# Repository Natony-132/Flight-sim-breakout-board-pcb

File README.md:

# Flight simulator control integration PCB 

This project was to make a simple, expandable, Hardware to USB input control board. This is so that additional, non-standard controls or switch panels can be added to an existing flight simulator setup. 

This was accomplished by using an existing Arduino program called FreeJoy with a custom Interface board. The freeJoy program allows a series of Shift registers to expand the number of inputs that an arduino can normally except. 

This custom PCB was designed with 40 inputs for switches and pads for up to 4 potentiometers.  

Due to signal noise in most potentiometers, each pad was designed to have a 3rd order filter built in. 

This proved to be unnecessary due to filters built into the Arduino program. This was not unexpected, so a filter bypass was built into the PCB so that the physical filter doesn't need to not be populated during board assembly. 

Later iterations will leave off this filter entirely.

These custom circuit boards were used in a UH-34 Sikorsky helicopter collective and a replica FA18 landing gear panel.

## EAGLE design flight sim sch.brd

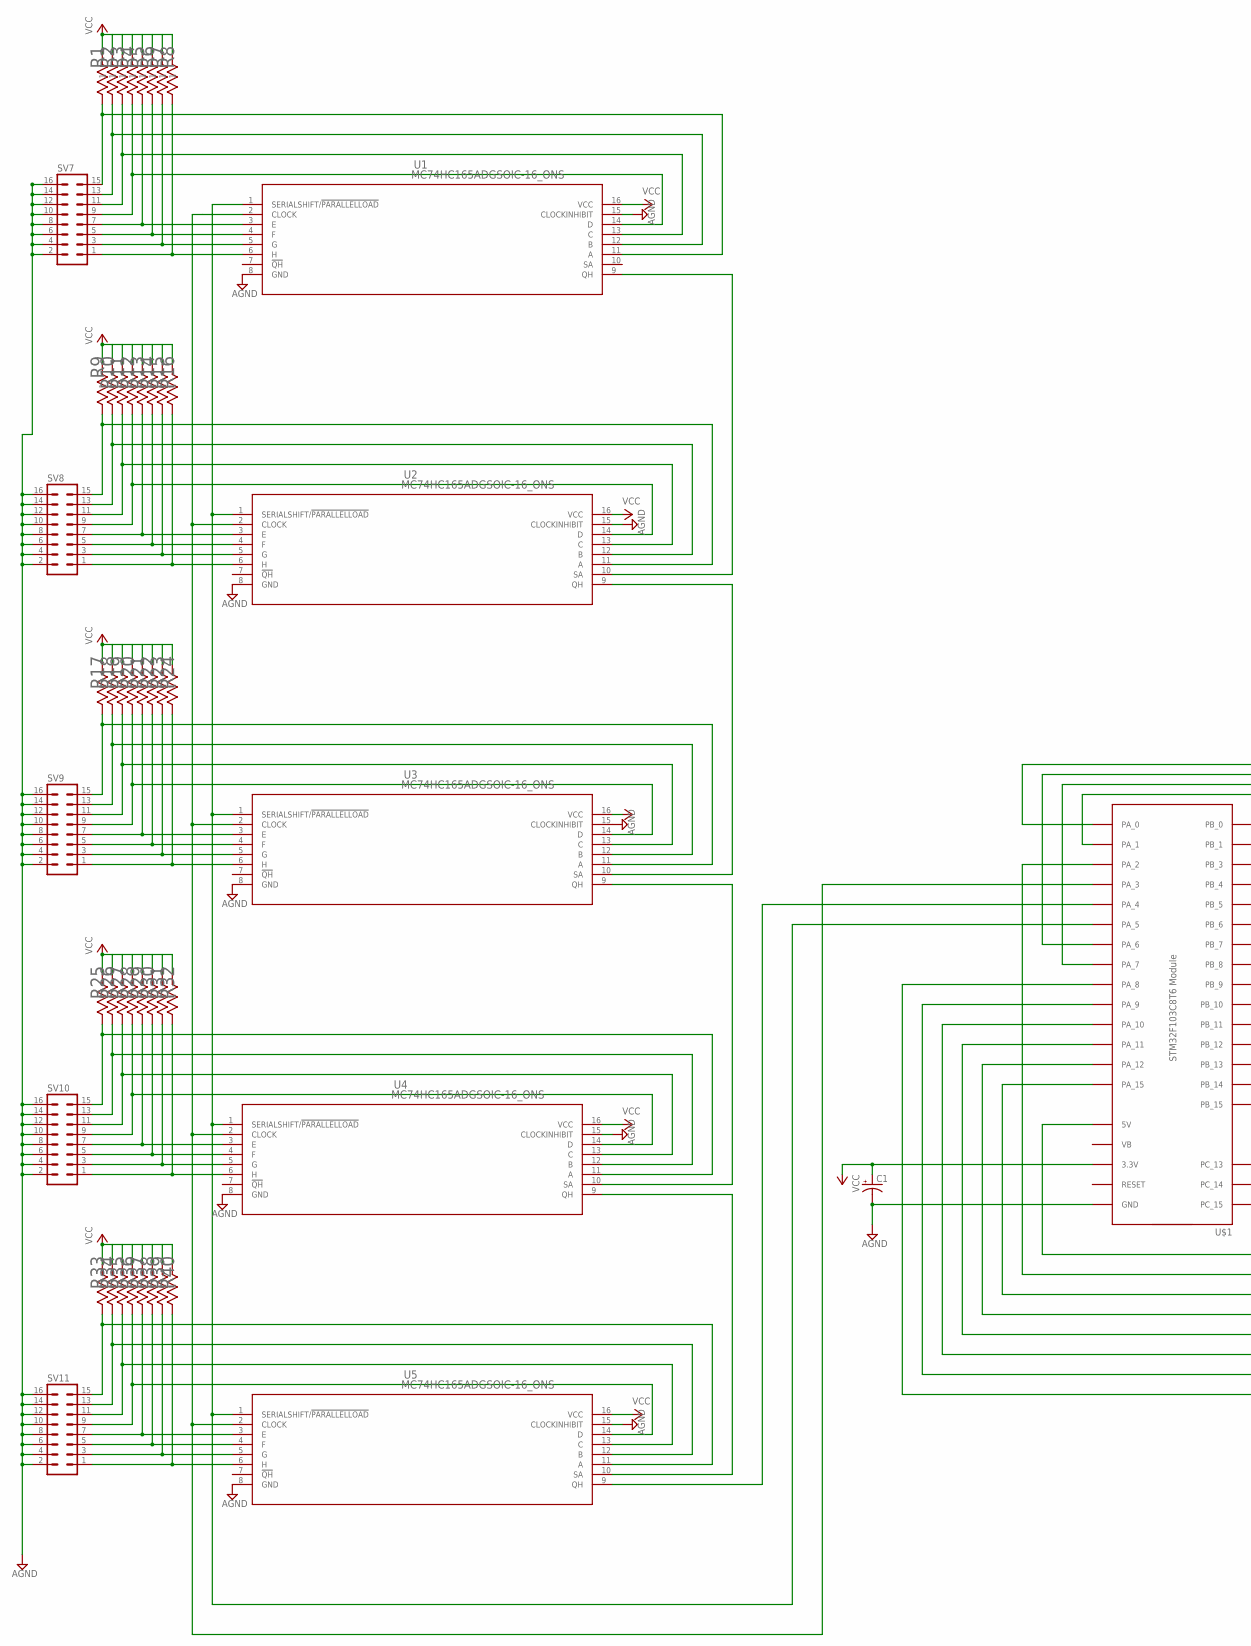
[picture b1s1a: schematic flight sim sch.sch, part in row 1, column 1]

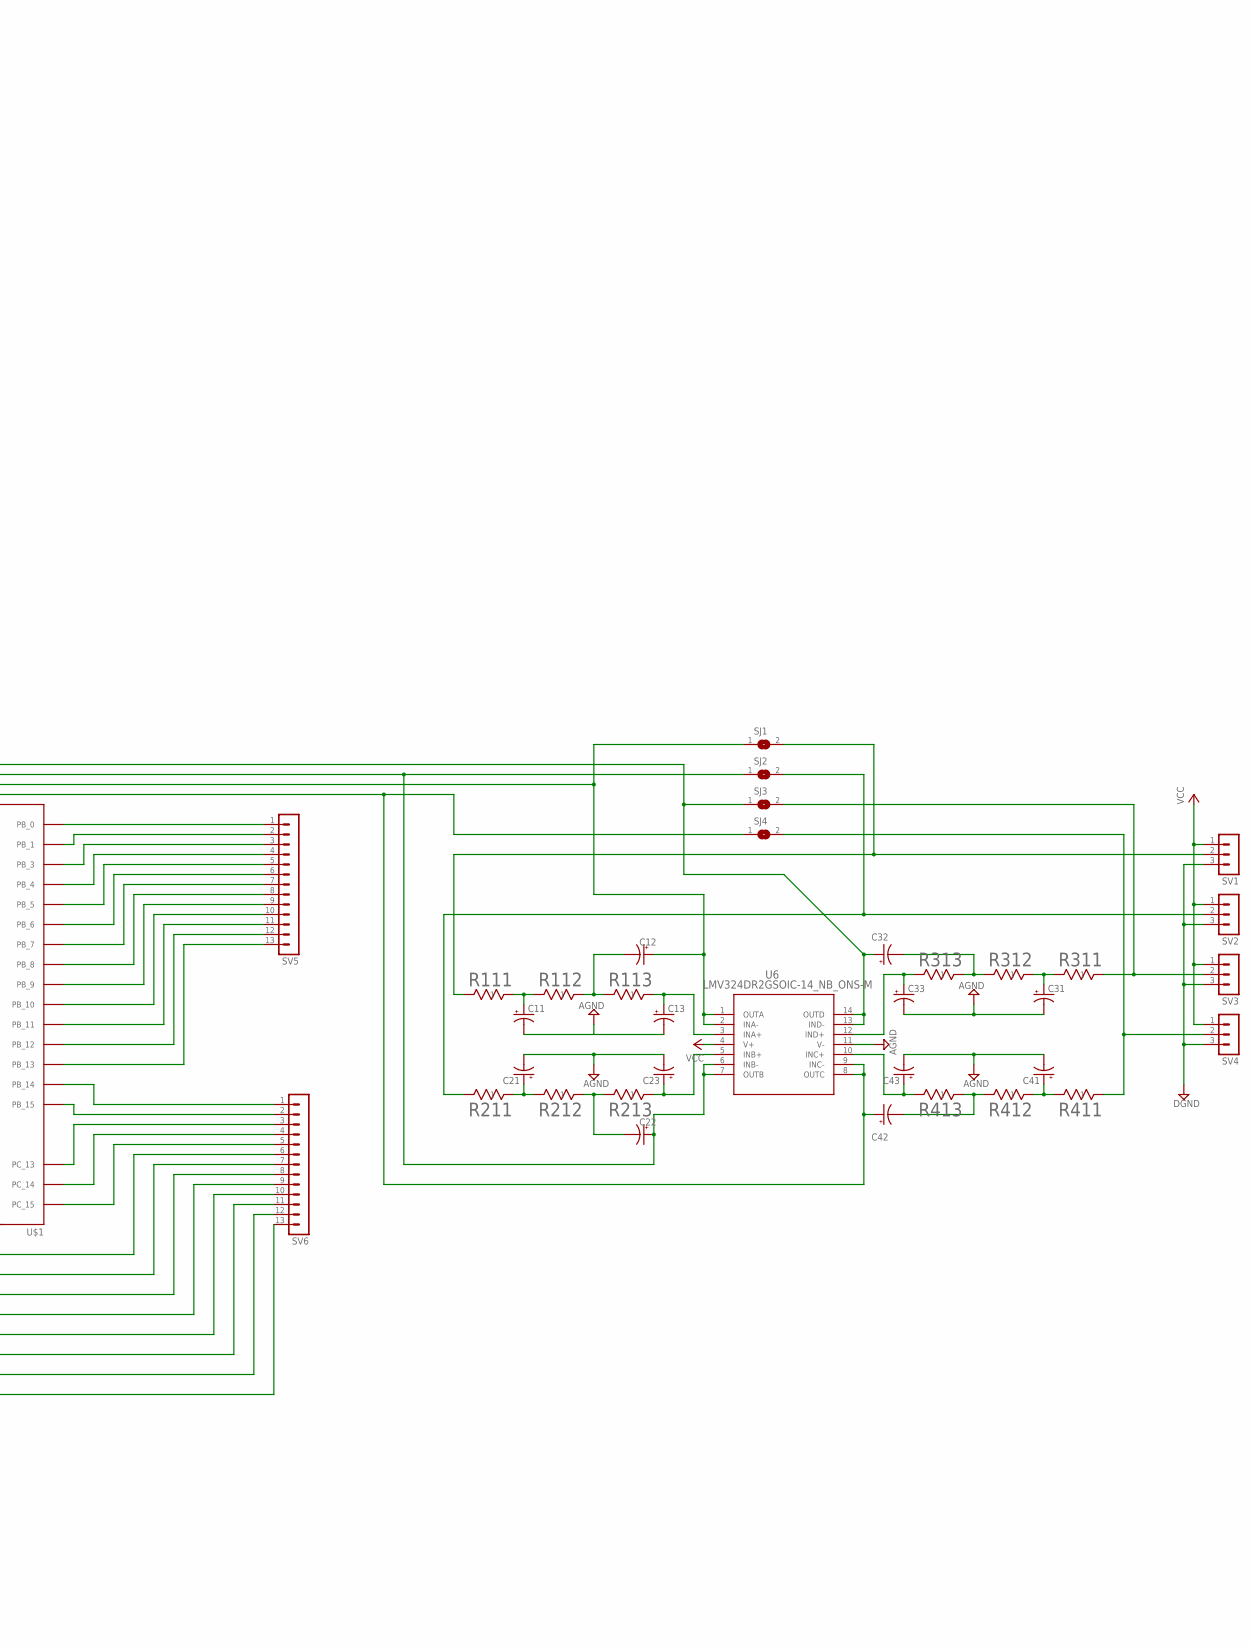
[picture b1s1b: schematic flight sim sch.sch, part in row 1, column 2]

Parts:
C1, C11, C12, C13, C21, C22, C23, C31, C32, C33, C41, C42, C43: CPOL-USE1.8-4; E1,8-4
R1, R2, R3, R4, R5, R6, R7, R8, R9, R10, R11, R12, R13, R14, R15, R16, R17, R18, R19, R20, R21, R22, R23, R24, R25, R26, R27, R28, R29, R30, R31, R32, R33, R34, R35, R36, R37, R38, R39, R40, R111, R112, R113, R211, R212, R213, R311, R312, R313, R411, R412, R413: MFR-25FRF52-10KYAG_MF25_YAG; YAG_MF25_YAG
SJ1, SJ2, SJ3, SJ4: SJ
SV1, SV2, SV3, SV4: MA03-1
SV5, SV6: MA13-1
SV7, SV8, SV9, SV10, SV11: MA08-2
U1, U2, U3, U4, U5: MC74HC165ADGSOIC-16_ONS; SOIC-16_ONS
U6: LMV324DR2GSOIC-14_NB_ONS-M; SOIC-14_NB_ONS-M
U$1: STM32F103C8T6-MODULE

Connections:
AGND: C1.-, C11.-, C13.-, C21.-, C23.-, C31.-, C33.-, C41.-, C43.-, SV7.2, SV7.4, SV7.6, SV7.8, SV7.10, SV7.12, SV7.14, SV7.16, SV8.2, SV8.4, SV8.6, SV8.8, SV8.10, SV8.12, SV8.14, SV8.16, SV9.2, SV9.4, SV9.6, SV9.8, SV9.10, SV9.12, SV9.14, SV9.16, SV10.2, SV10.4, SV10.6, SV10.8, SV10.10, SV10.12, SV10.14, SV10.16, SV11.2, SV11.4, SV11.6, SV11.8, SV11.10, SV11.12, SV11.14, SV11.16, U1.8 (GND), U1.15 (CLOCKINHIBIT), U2.8 (GND), U2.15 (CLOCKINHIBIT), U3.8 (GND), U3.15 (CLOCKINHIBIT), U4.8 (GND), U4.15 (CLOCKINHIBIT), U5.8 (GND), U5.15 (CLOCKINHIBIT), U6.11 (V-), U$1.GND@1 (GND), U$1.GND@2 (GND), U$1.GND@3 (GND)
DGND: SV1.3, SV2.3, SV3.3, SV4.3
unnamed: U1.9 (QH), U2.10 (SA)
unnamed: R8.2, SV7.1, U1.6 (H)
unnamed: R7.2, SV7.3, U1.5 (G)
unnamed: R6.2, SV7.5, U1.4 (F)
unnamed: R5.2, SV7.7, U1.3 (E)
unnamed: R4.2, SV7.9, U1.14 (D)
unnamed: R3.2, SV7.11, U1.13 (C)
unnamed: R2.2, SV7.13, U1.12 (B)
unnamed: R1.2, SV7.15, U1.11 (A)
unnamed: U1.2 (CLOCK), U2.2 (CLOCK), U3.2 (CLOCK), U4.2 (CLOCK), U5.2 (CLOCK), U$1.PA_3
unnamed: R16.2, SV8.1, U2.6 (H)
unnamed: R15.2, SV8.3, U2.5 (G)
unnamed: R14.2, SV8.5, U2.4 (F)
unnamed: R13.2, SV8.7, U2.3 (E)
unnamed: R24.2, SV9.1, U3.6 (H)
unnamed: R23.2, SV9.3, U3.5 (G)
unnamed: R22.2, SV9.5, U3.4 (F)
unnamed: R21.2, SV9.7, U3.3 (E)
unnamed: R20.2, SV9.9, U3.14 (D)
unnamed: R19.2, SV9.11, U3.13 (C)
unnamed: R18.2, SV9.13, U3.12 (B)
unnamed: R12.2, SV8.9, U2.14 (D)
unnamed: R32.2, SV10.1, U4.6 (H)
unnamed: R31.2, SV10.3, U4.5 (G)
unnamed: R30.2, SV10.5, U4.4 (F)
unnamed: R29.2, SV10.7, U4.3 (E)
unnamed: R28.2, SV10.9, U4.14 (D)
unnamed: R27.2, SV10.11, U4.13 (C)
unnamed: R26.2, SV10.13, U4.12 (B)
unnamed: R33.2, SV11.15, U5.11 (A)
unnamed: R25.2, SV10.15, U4.11 (A)
unnamed: R34.2, SV11.13, U5.12 (B)
unnamed: R11.2, SV8.11, U2.13 (C)
unnamed: R35.2, SV11.11, U5.13 (C)
unnamed: R36.2, SV11.9, U5.14 (D)
unnamed: R37.2, SV11.7, U5.3 (E)
unnamed: R38.2, SV11.5, U5.4 (F)
unnamed: R39.2, SV11.3, U5.5 (G)
unnamed: U2.9 (QH), U3.10 (SA)
unnamed: C11.+, R111.1, R112.2
unnamed: U3.9 (QH), U4.10 (SA)
unnamed: U4.9 (QH), U5.10 (SA)
unnamed: U5.9 (QH), U$1.PA_4
unnamed: U1.1 (SERIALSHIFT/!PARALLELLOAD), U2.1 (SERIALSHIFT/!PARALLELLOAD), U3.1 (SERIALSHIFT/!PARALLELLOAD), U4.1 (SERIALSHIFT/!PARALLELLOAD), U5.1 (SERIALSHIFT/!PARALLELLOAD), U$1.PA_5
unnamed: R40.2, SV11.1, U5.6 (H)
unnamed: C22.-, R212.1, R213.2
unnamed: C21.+, R211.1, R212.2
unnamed: C13.+, R113.1, U6.3 (INA+)
unnamed: C12.+, SJ1.1, U6.1 (OUTA), U6.2 (INA-), U$1.PA_7
unnamed: C12.-, R112.1, R113.2
unnamed: R10.2, SV8.13, U2.12 (B)
unnamed: R9.2, SV8.15, U2.11 (A)
unnamed: C42.-, R412.2, R413.1
unnamed: C23.+, R213.1, U6.5 (INB+)
unnamed: R17.2, SV9.15, U3.11 (A)
unnamed: C33.+, R313.2, U6.12 (IND+)
unnamed: C31.+, R311.2, R312.1
unnamed: C43.+, R413.2, U6.10 (INC+)
unnamed: C41.+, R411.2, R412.1
unnamed: C32.-, R312.2, R313.1
unnamed: SV6.7, U$1.PA_2
unnamed: SV6.6, U$1.5V
N$A8: SV6.13, U$1.PA_8
N$A9: SV6.12, U$1.PA_9
N$A10: SV6.11, U$1.PA_10
N$A11: SV6.10, U$1.PA_11
N$A12: SV6.9, U$1.PA_12
N$A15: SV6.8, U$1.PA_15
N$B0: SV5.1, U$1.PB_0
N$B1: SV5.2, U$1.PB_1
N$B3: SV5.3, U$1.PB_3
N$B4: SV5.4, U$1.PB_4
N$B5: SV5.5, U$1.PB_5
N$B6: SV5.6, U$1.PB_6
N$B7: SV5.7, U$1.PB_7
N$B8: SV5.8, U$1.PB_8
N$B9: SV5.9, U$1.PB_9
N$B10: SV5.10, U$1.PB_10
N$B11: SV5.11, U$1.PB_11
N$B12: SV5.12, U$1.PB_12
N$B13: SV5.13, U$1.PB_13
N$B14: SV6.1, U$1.PB_14
N$B15: SV6.2, U$1.PB_15
N$C13: SV6.3, U$1.PC_13
N$C14: SV6.4, U$1.PC_14
N$C15: SV6.5, U$1.PC_15
N$FILTER2OUT: C22.+, SJ2.1, U6.6 (INB-), U6.7 (OUTB), U$1.PA_6
N$FILTER3OUT: C32.+, SJ3.1, U6.13 (IND-), U6.14 (OUTD), U$1.PA_0
N$FILTER4OUT: C42.+, SJ4.1, U6.8 (OUTC), U6.9 (INC-), U$1.PA_1
N$POT1IN: R111.2, SJ1.2, SV1.2
N$POT2IN: R211.2, SJ2.2, SV2.2
N$POT3IN: R311.1, SJ3.2, SV3.2
N$POT4IN: R411.1, SJ4.2, SV4.2
VCC: C1.+, R1.1, R2.1, R3.1, R4.1, R5.1, R6.1, R7.1, R8.1, R9.1, R10.1, R11.1, R12.1, R13.1, R14.1, R15.1, R16.1, R17.1, R18.1, R19.1, R20.1, R21.1, R22.1, R23.1, R24.1, R25.1, R26.1, R27.1, R28.1, R29.1, R30.1, R31.1, R32.1, R33.1, R34.1, R35.1, R36.1, R37.1, R38.1, R39.1, R40.1, SV1.1, SV2.1, SV3.1, SV4.1, U1.16 (VCC), U2.16 (VCC), U3.16 (VCC), U4.16 (VCC), U5.16 (VCC), U6.4 (V+), U$1.3.3V@1 (3.3V), U$1.3.3V@2 (3.3V)

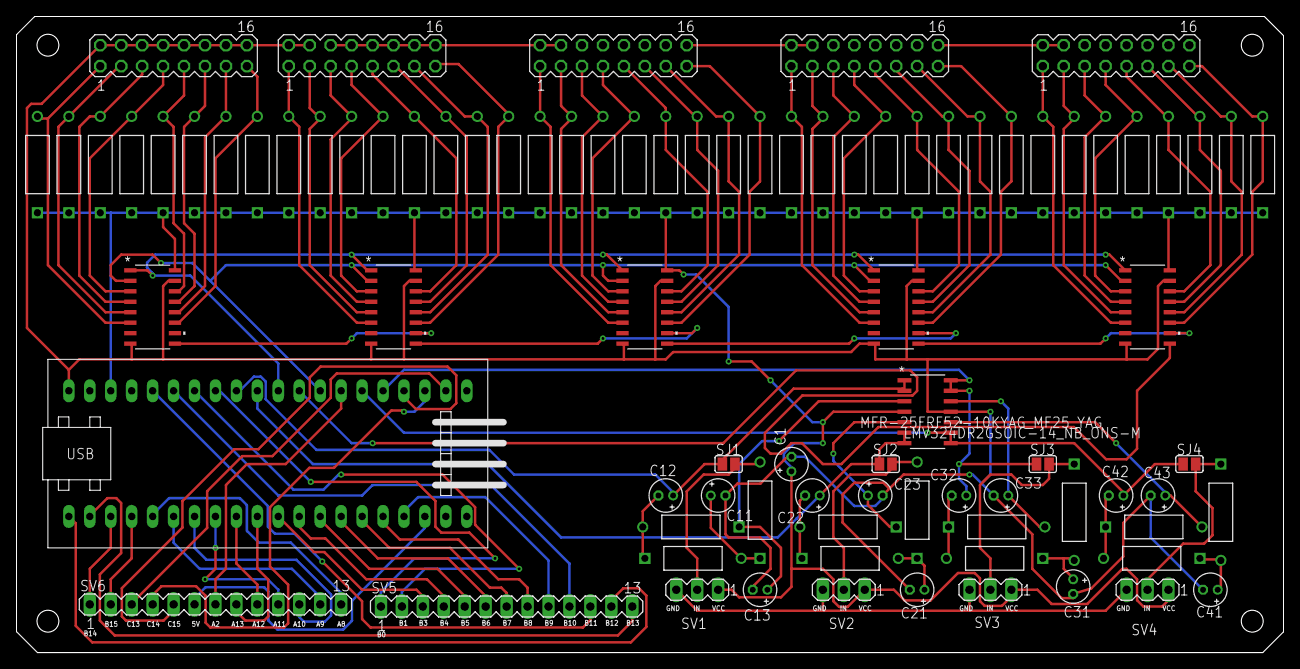
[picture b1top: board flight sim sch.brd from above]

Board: 2 copper layers, 153.7 x 77.1 mm, 87 parts (0 on the bottom side), 96 nets.

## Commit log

2022-07-18 Create info dump
2022-07-20 Create board
2022-07-21 trial layout ideas
2024-07-01 images!
2024-07-01 fixed the name
2024-07-01 naming for the images
2024-07-01 new pics
2024-07-01 Create Flight sim PCB in use
2024-07-01 new folder
2024-07-01 new images
2024-07-01 more pics
2024-07-01 MORE!

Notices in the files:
parts and their libraries:
COPYRIGHT: Copyright (C) 2022 Ultra Librarian. All rights reserved.
